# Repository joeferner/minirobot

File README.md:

# Minirobot

# Microcontroller Pin Requirements

| Name                    | Requirements                    | Pin                   |
| ----------------------- | ------------------------------- | --------------------- |
| Debug                   | UART TX/RX                      | UART1-PA9/PA10        |
| Wheel encoder left      | EXTI                            | PB0                   |
| Wheel encoder right     | EXTI                            | PB1                   |
| Wheel servo left        | PWM                             | TIM3-PA6              |
| Wheel servo right       | PWM                             | TIM3-PA7              |
| Line follow left outer  | EXTI                            | PB12                  |
| Line follow right outer | EXTI                            | PB14                  |
| Line follow left inner  | EXTI                            | PB13                  |
| Line follow right inner | EXTI                            | PB15                  |
| I<sup>2</sup>C1         | SCL/SDA                         | PB8/PB9               |
| Compass (ST-LIS3MDL)    | I<sup>2</sup>C (0x1E)           | I<sup>2</sup>C1       |
| Color Sensor (TCS3472)  | I<sup>2</sup>C (0x29)           | I<sup>2</sup>C1       |
| Color Sensor Interrupt  | GPIO IN                         | PB6                   |
| Color LED               | PWM                             | TIM4-PB7              |
| Bluetooth (RN4020)      | USART TX/RX/CTS/RTS             | UART2-PA2/PA3/PA0/PA1 |
| Bluetooth MLDP          | GPIO OUT                        | PC1                   |
| Bluetooth WakeSW        | GPIO OUT                        | PC2                   |
| Bluetooth WakeHW        | GPIO OUT                        | PC3                   |
| Bluetooth WS            | GPIO IN                         | PA4                   |
| Bluetooth Connection    | GPIO IN                         | PA5                   |
| Bluetooth MLDPEV        | GPIO IN                         | PC4                   |
| Battery level           | ADC                             | VBAT                  |

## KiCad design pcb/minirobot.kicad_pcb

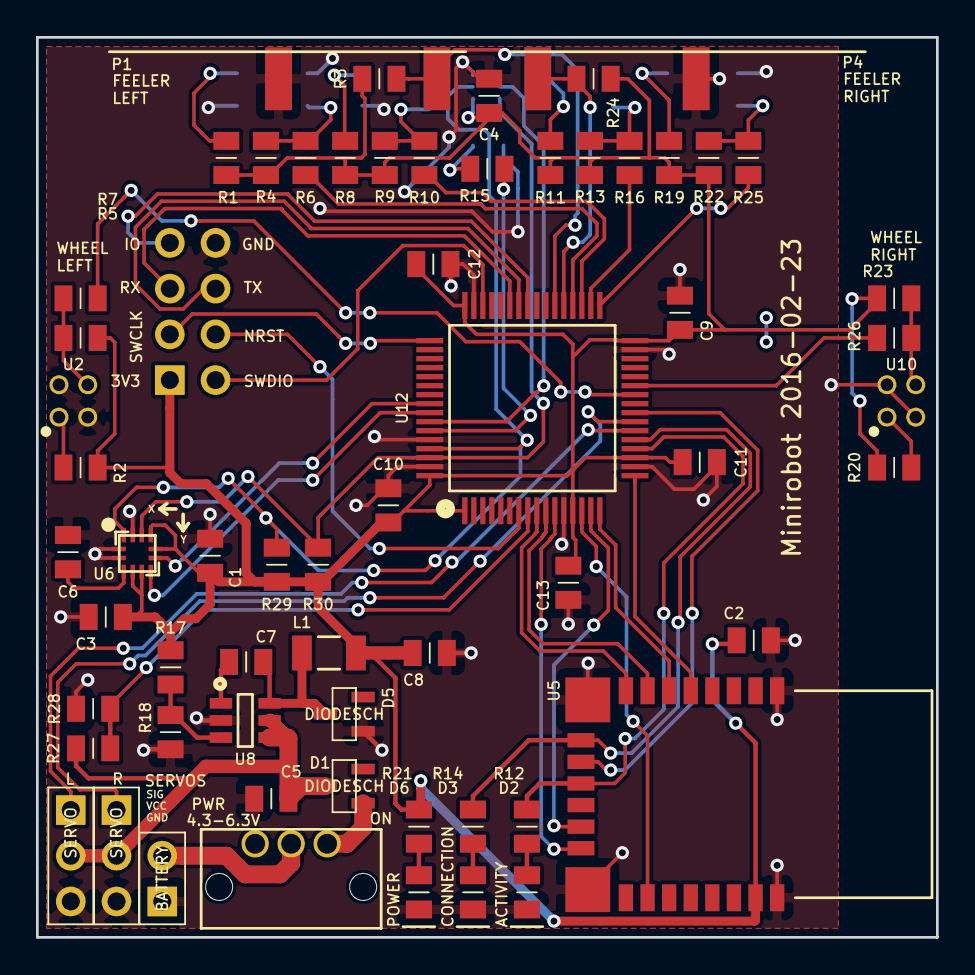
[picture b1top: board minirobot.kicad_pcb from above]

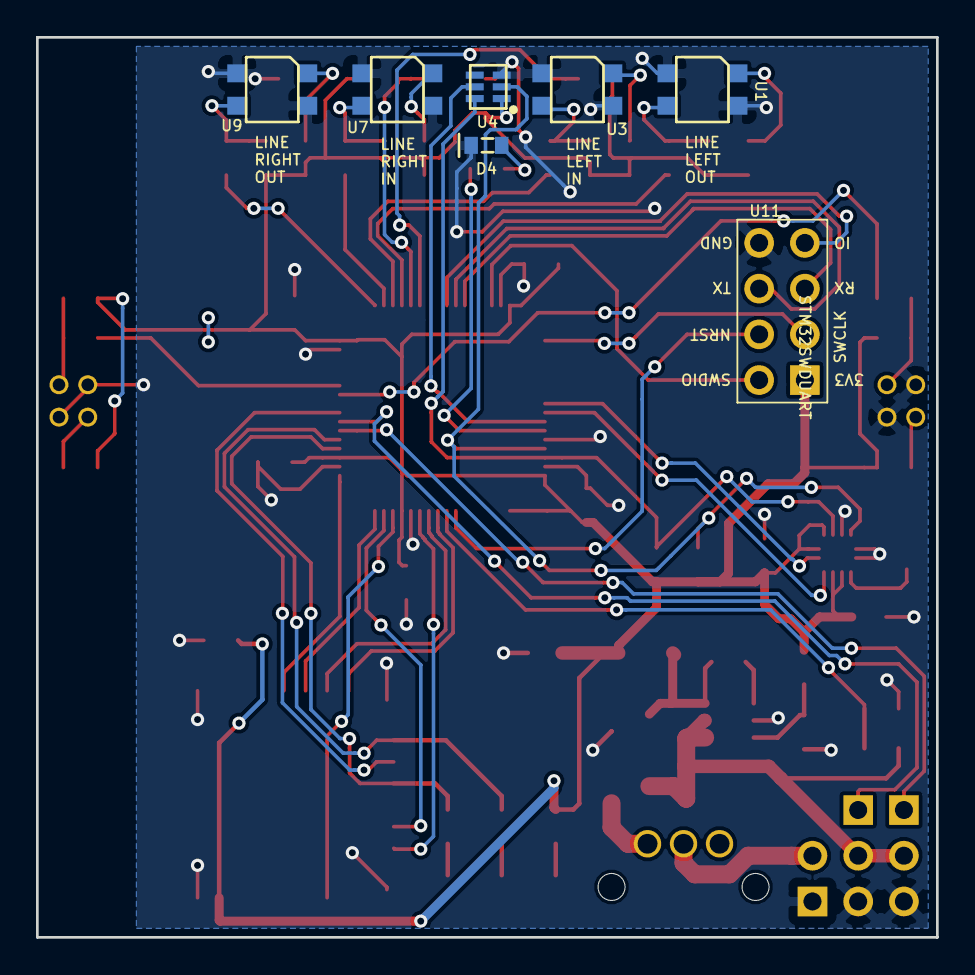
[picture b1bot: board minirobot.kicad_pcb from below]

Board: 2 copper layers, 50.0 x 50.0 mm, 68 parts (7 on the bottom side), 58 nets.

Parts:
C1, C4, C6, C9, C10, C11, C12, C13: 0.1uF; CAPC2012X100N
C2, C8: 10uF; CAPC2012X100N
C3: 1uF; CAPC2012X100N
C5: 10uF >6V; CAPC2012X100N
C7: 0.012uF; CAPC2012X100N
D1, D5: DIODESCH; SOT95P237X112_132-3N
D2: ACTIVITY-BLUE; LEDC2012X100N
D3: CONN-GREEN; LEDC2012X100N
D4: LED; LEDC1608X40N
D6: 3V3LED; LEDC2012X100N
L1: 4.7uH; INDC3218X180N
P1: FEELERLEFT; OMRON-SS-5GL-F-3-RAM
P2, P5: SERVO; HDRV3W66P254_1X3_762X249X838P
P3: BATTERY; HDRV2W66P254_1X2_508X249X838P
P4: FEELERRIGHT; OMRON-SS-5GL-F-3-RA
R1, R2, R8, R11, R15, R19, R20: 51R; RESC2012X100N
R3, R4, R5, R9, R13, R22, R23, R24, R27, R28: 10K; RESC2012X100N
R6, R7, R10, R16, R25, R26: 0R; RESC2012X100N
R12, R14, R21: 100R; RESC2012X100N
R17: 62K; RESC2012X100N
R18: 20K; RESC2012X100N
R29, R30: 4.7K; RESC2012X100N
S1: POWER; COPAL-MFS101D-6-Z
U1: LINELEFTOUT; QRE1113GR
U2: WHEELLEFT; QRE1113-RA
U3: LINELEFTIN; QRE1113GR
U4: TCS3472
U5: RN4020
U6: ST-LIS3MDL; LGA12S50P4X4_192X192X100
U7: LINERIGHTIN; QRE1113GR
U8: DIODES-AP3211; SOT95P270X145-6N
U9: LINERIGHTOUT; QRE1113GR
U10: WHEELRIGHT; QRE1113-RA
U11: STM32SWDUART; HDRV8W64P254_2X4_1016X483X838P
U12: STM32F411RET6; QFP50P1200X1200X160-64N

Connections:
+3.3V: C1.1, C2.1, C3.1, C4.1, C8.1, C9.1, C10.1, C11.1, C12.1, C13.1, L1.1, R1.1, R2.1, R3.2, R4.2, R5.2, R8.1, R9.2, R11.1, R13.2, R17.1, R19.1, R20.1, R21.1, R22.2, R23.2, R24.2, R29.1, R30.1, U4.1, U5.23, U6.5, U6.6, U6.9, U6.10, U11.1, U12.1, U12.13, U12.19, U12.32, U12.48, U12.64
/Bluetooth/BLECONN: R14.1, U5.10, U12.21
/Bluetooth/BLEMLDP: U5.8, U12.9
/Bluetooth/BLEMLDPEV: U5.11, U12.24
/Bluetooth/BLEUARTCTS: U5.14, U12.15
/Bluetooth/BLEUARTRTS: U5.18, U12.14
/Bluetooth/BLEUARTRX: U5.6, U12.16
/Bluetooth/BLEUARTTX: U5.5, U12.17
/Bluetooth/BLEWAKEHW: U5.15, U12.11
/Bluetooth/BLEWAKESW: U5.7, U12.10
/Bluetooth/BLEWS: R12.1, U5.12, U12.20
/Compass/COMPASSINT: U6.7, U12.57
/Compass/COMPASSRDY: U6.8, U12.56
/Compass/I2CSCL: R29.2, U4.2, U6.1, U12.61
/Compass/I2CSDA: R30.2, U4.6, U6.11, U12.62
/DEBUGGPIO: U11.7, U12.41
/DEBUGRX: U11.5, U12.43
/DEBUGTX: U11.6, U12.42
/NRST: U11.4, U12.7
/SWCLK: U11.3, U12.49
/SWDIO: U11.2, U12.46
/Sensors/COLORINT: U4.5, U12.58
/Sensors/COLORLED: R15.2, U12.59
/Sensors/FEELERLEFT: P1.1, R3.1, U12.38
/Sensors/FEELERRIGHT: P4.1, R24.1, U12.37
/Sensors/LINELEFTIN: R10.1, U12.35
/Sensors/LINELEFTOUT: R6.1, U12.36
/Sensors/LINERIGHTIN: R16.1, U12.34
/Sensors/LINERIGHTOUT: R25.1, U12.33
/Sensors/SERVOLEFT: P2.1, U12.22
/Sensors/SERVORIGHT: P5.1, U12.23
/Sensors/WHEELLEFT: R7.1, U12.26
/Sensors/WHEELRIGHT: R26.1, U12.27
/VBAT: R27.2, R28.1, U12.8
GNDPWR: C1.2, C2.2, C3.2, C4.2, C5.2, C6.2, C8.2, C9.2, C10.2, C11.2, C12.2, C13.2, D2.2, D3.2, D4.2, D5.1, D6.2, P1.2, P2.3, P3.1, P4.2, P5.3, R18.2, R28.2, U1.2, U1.4, U2.2, U2.4, U3.2, U3.4, U4.3, U5.1, U5.9, U5.16, U5.24, U6.2, U6.3, U6.12, U7.2, U7.4, U8.2, U9.2, U9.4, U10.2, U10.4, U11.8, U12.12, U12.18, U12.31, U12.47, U12.60, U12.63
unnamed: C6.1, U6.4
unnamed: C7.1, U8.1
unnamed: C7.2, D5.2, L1.2, U8.6
unnamed: D1.1, S1.3
unnamed: D2.1, R12.2
unnamed: D3.1, R14.2
unnamed: D4.1, R15.1
unnamed: D6.1, R21.2
unnamed: P3.2, S1.2
unnamed: R1.2, U1.1
unnamed: R2.2, U2.1
unnamed: R4.1, R6.2, U1.3
unnamed: R5.1, R7.2, U2.3
unnamed: R8.2, U3.1
unnamed: R9.1, R10.2, U3.3
unnamed: R11.2, U7.1
unnamed: R13.1, R16.2, U7.3
unnamed: R17.2, R18.1, U8.3
unnamed: R19.2, U9.1
unnamed: R20.2, U10.1
unnamed: R22.1, R25.2, U9.3
unnamed: R23.1, R26.2, U10.3
Vcc: C5.1, D1.2, P2.2, P5.2, R27.1, U8.4, U8.5

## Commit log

2016-01-12 initial
2016-01-12 initial mechanical
2016-01-12 update gitignore
2016-01-21 initial schematic
2016-01-21 add compass
2016-01-22 battery level
2016-01-25 update schematics
2016-01-25 assign inventory ids
2016-01-26 more schematics
2016-01-30 initial part layout
2016-02-11 pcb routing complete
2016-02-22 finish layout
2016-02-29 2016-02-23 pcb
2016-03-19 blink
2016-03-19 debug uart working
2016-03-19 working compass comms
2016-03-19 extend compass leads to help with rework
2016-03-19 add compass x/y markings on silk
2016-03-19 move SWD/Debug connector to make it easier for compass rework
2016-03-26 working servo
2016-03-26 feeler irq
2016-03-26 working line and wheel sensors
2016-03-27 working color sensor
2016-03-28 working BLE and battery level
2016-03-28 format code
2016-03-30 working BLE connect and battery level
2016-03-30 working reconnect
2016-03-31 support real time read of battery:
2016-04-01 get/set motor
2016-04-02 working reads
2016-04-02 write motor speed
2016-04-02 get/set config
2016-04-05 bottom test mech
2016-04-05 notify instead of polling
